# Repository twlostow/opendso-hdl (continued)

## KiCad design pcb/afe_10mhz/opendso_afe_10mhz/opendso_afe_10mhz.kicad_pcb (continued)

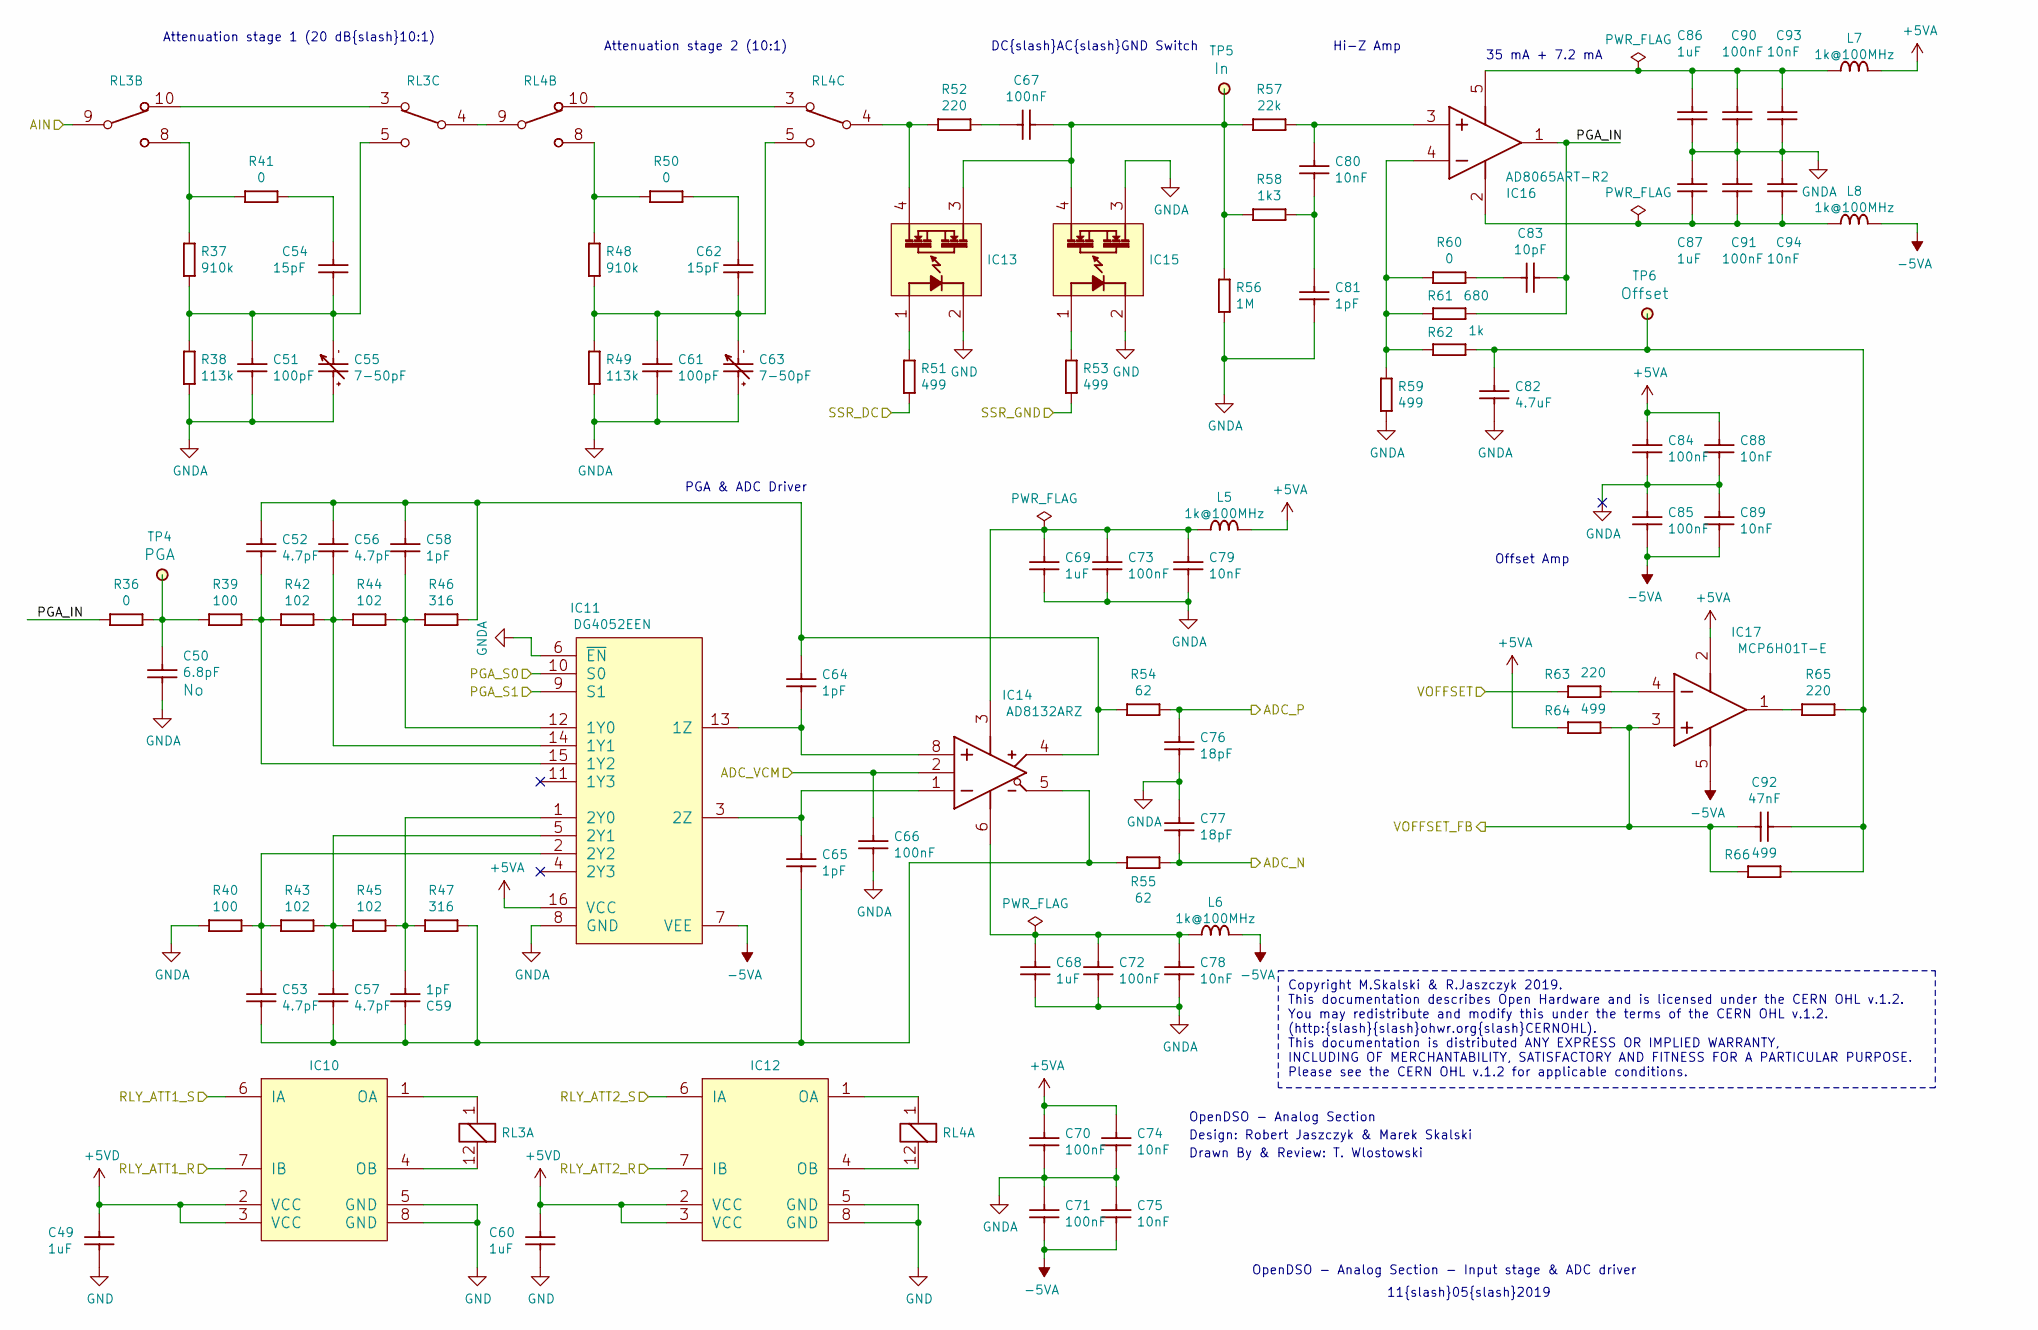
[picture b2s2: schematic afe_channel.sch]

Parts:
C49, C60, C68, C69, C86, C87: CC0603_1UF_16V_10%_X7R; CAPC1608X87N; Voltage 16V; Tolerance ±10%; Part Number CC0603_1UF_16V_10%_X7R
C50: CC0603_6.8PF_50V_0.5PF_NP0; CAPC1608X87N; Voltage 50V; Tolerance ±0.5pF; Part Number CC0603_6.8PF_50V_0.5PF_NP0
C51, C61: CC0603_100PF_50V_1%_NP0; CAPC1608X90N; Voltage 50V; Tolerance ±1%; Part Number CC0603_100PF_50V_1%_NP0
C52, C53, C56, C57: CC0603_4.7PF_50V_0.25PF_NP0; CAPC1608X87N; Voltage 50V; Tolerance ±0.25pF; Part Number CC0603_4.7PF_50V_0.25PF_NP0
C54, C62: CC0603_15PF_50V_5%_NP0; CAPC1608X87N; Voltage 50V; Tolerance ±5%; Part Number CC0603_15PF_50V_5%_NP0
C55, C63: CADJ_7-50PF_50V_MURATA_TZB4R500AB10R00; CAPV_MURATA_TZB4_TYPE A; Voltage 50V; Tolerance +100 -0%; Part Number CADJ_7-50PF_50V_MURATA_TZB4R500AB10R00
C58, C59, C64, C65, C81: CC0603_1PF_50V_0.25PF_NP0; CAPC1608X87N; Voltage 50V; Tolerance ±0.25pF; Part Number CC0603_1PF_50V_0.25PF_NP0
C66, C70, C71, C72, C73, C84, C85, C90, C91: CC0603_100NF_50V_10%_X7R; CAPC1608X87N; Voltage 50V; Tolerance ±10%; Part Number CC0603_100NF_50V_10%_X7R
C67: CC1206_100NF_100V_10%_X7R; CAPC3216X140N; Voltage 100V; Tolerance ±10%; Part Number CC1206_100NF_100V_10%_X7R
C74, C75, C78, C79, C80, C88, C89, C93, C94: CC0603_10NF_50V_5%_C0G; CAPC1608X87N; Voltage 50V; Tolerance ±5%; Part Number CC0603_10NF_50V_5%_C0G
C76, C77: CC0603_18PF_50V_5%_NP0; CAPC1608X87N; Voltage 50V; Tolerance ±5%; Part Number CC0603_18PF_50V_5%_NP0
C82: CC0805_4.7UF_16V_10%_X7R; CAPC2012X135N; Voltage 16V; Tolerance ±10%; Part Number CC0805_4.7UF_16V_10%_X7R
C83: CC0603_10PF_50V_5%_NP0; CAPC1608X87N; Voltage 50V; Tolerance ±5%; Part Number CC0603_10PF_50V_5%_NP0
C92: CC0603_47NF_25V_10%_X7R; CAPC1608X87N; Voltage 25V; Tolerance ±10%; Part Number CC0603_47NF_25V_10%_X7R
IC10, IC12: L9110; SOIC127P1030X265-20N; Part Number MC100LVEL14DWG
IC11: DG4052EEN; SOP65P640X110-16N; Part Number 74HCT4052PW
IC13, IC15: VO1400AEFTR; VISHAY_VO1400AEF; Part Number VO1400AEFTR
IC14: AD8132ARZ; SOIC127P600X175-8N; Part Number AD8132ARZ
IC16: AD8065ART-R2; SOT95P280X145-5N; Part Number AD8065ART-R2
IC17: MCP6H01T-E; SOT95P280X145-5N; Part Number MCP6H01T-E
L5, L6, L7, L8: IND0603_MURATA_BLM18AG102SN1; INDC1608X95N; Tolerance ±25%; Part Number IND0603_MURATA_BLM18AG102SN1
R36, R41, R50, R60: R0603_0R_JUMPER; RESC1608X55N; Voltage ~~; Tolerance ~~; Part Number R0603_0R_JUMPER
R37, R48: R0603_910K_1%_0.1W_100PPM; RESC1608X55N; Voltage ~~; Tolerance ±1%; Part Number R0603_910K_1%_0.1W_100PPM
R38, R49: R0603_113K_0.1%_0.063W_10PPM; RESC1608X55N; Voltage ~~; Tolerance ±0.1%; Part Number R0603_113K_0.1%_0.063W_10PPM
R39, R40: R0603_100R_1%_0.1W_100PPM; RESC1608X55N; Tolerance ±1%; Part Number R0603_100R_1%_0.1W_100PPM
R42, R43, R44, R45: R0603_102R_0.1%_0.063W_10PPM; RESC1608X55N; Tolerance ±0.1%; Part Number R0603_102R_0.1%_0.063W_10PPM
R46, R47: R0603_316R_0.1%_0.063W_10PPM; RESC1608X55N; Tolerance ±0.1%; Part Number R0603_316R_0.1%_0.063W_10PPM
R51, R53, R59, R64, R66: R0603_499R_0.1%_0.063W_10PPM; RESC1608X55N; Voltage ~~; Tolerance ±0.1%; Part Number R0603_499R_0.1%_0.063W_10PPM
R52, R63, R65: R0603_220R_1%_0.1W_100PPM; RESC1608X55N; Voltage ~~; Tolerance ±1%; Part Number R0603_220R_1%_0.1W_100PPM
R54, R55: R0603_62R_1%_0.1W_100PPM; RESC1608X55N; Tolerance ±1%; Part Number R0603_62R_1%_0.1W_100PPM
R56: R0603_1M_1%_0.1W_100PPM; RESC1608X55N; Voltage ~~; Tolerance ±1%; Part Number R0603_1M_1%_0.1W_100PPM
R57: R0603_22K_1%_0.1W_100PPM; RESC1608X55N; Voltage ~~; Tolerance ±1%; Part Number R0603_22K_1%_0.1W_100PPM
R58: R0603_1K3_1%_0.1W_100PPM; RESC1608X55N; Voltage ~~; Tolerance ±1%; Part Number R0603_1K3_1%_0.1W_100PPM
R61: R0603_680R_0.1%_0.1W_25PPM; RESC1608X64N; Voltage ~~; Tolerance ±0.1%; Part Number R0603_680R_0.1%_0.1W_25PPM
R62: R0603_1K_1%_0.1W_100PPM; RESC1608X55N; Voltage ~~; Tolerance ±1%; Part Number R0603_1K_1%_0.1W_100PPM
RL3, RL4: REL_OMRON_G6SU-2F-5VDC; Relay_DPDT_Omron_G6SU-2F; Part Description DPDT Signal Relay, Ultracompact and Ult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
TP4: PGA; TPS127; Part Number SMD_PAD_1.27X1.27MM
TP5: In; TPS127; Part Number SMD_PAD_1.27X1.27MM
TP6: Offset; TPS127; Part Number SMD_PAD_1.27X1.27MM

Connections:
+5VA: C70.2, C74.2, C84.2, C88.2, IC11.16 (VCC), IC17.2 (V-), L5.2, L7.2, R64.2; also elsewhere on the board
+5VD: C49.2, C60.2, IC10.2 (VCC), IC10.3 (VCC), IC12.2 (VCC), IC12.3 (VCC); also elsewhere on the board
-5VA: C71.1, C75.1, C85.1, C89.1, IC11.7 (VEE), IC17.5 (V+), L6.2, L8.2; also elsewhere on the board
/ADC_N: C77.1, R55.2; also elsewhere on the board
/ADC_P: C76.2, R54.2; also elsewhere on the board
/AFE Channel 1/PGA_IN: C83.2, IC16.1 (OUT), R36.1, R61.2
/AIN_1: RL3.9 (C); also elsewhere on the board
/CH1_PGA_S0: IC11.10 (S0); also elsewhere on the board
/CH1_PGA_S1: IC11.9 (S1); also elsewhere on the board
/CH1_RLY_ATT1_R: IC10.7 (IB); also elsewhere on the board
/CH1_RLY_ATT1_S: IC10.6 (IA); also elsewhere on the board
/CH1_RLY_ATT2_R: IC12.7 (IB); also elsewhere on the board
/CH1_RLY_ATT2_S: IC12.6 (IA); also elsewhere on the board
/CH1_SSR_DC: R51.1; also elsewhere on the board
/CH1_SSR_GND: R53.1; also elsewhere on the board
/CH1_VCM: C66.2, IC14.2 (VOCM); also elsewhere on the board
/CH1_VOFFSET: R63.1; also elsewhere on the board
/CH1_VOFFSET_FB: C92.1, IC17.3 (IN+), R64.1, R66.2; also elsewhere on the board
unnamed: C50.1, R36.2, R39.1, TP4.1
unnamed: C51.2, C54.1, C55.2, R37.1, R38.2, RL3.5 (NO)
unnamed: C52.1, IC11.15 (1Y2), R39.2, R42.1
unnamed: C52.2, C56.2, C58.2, C64.2, IC14.4 (VOUT+), R46.2, R54.1
unnamed: C53.1, C57.1, C59.2, C65.1, IC14.5 (VOUT-), R47.2, R55.1
unnamed: C53.2, IC11.2 (2Y2), R40.2, R43.1
unnamed: C54.2, R41.2
unnamed: C56.1, IC11.14 (1Y1), R42.2, R44.1
unnamed: C57.2, IC11.5 (2Y1), R43.2, R45.1
unnamed: C58.1, IC11.12 (1Y0), R44.2, R46.1
unnamed: C59.1, IC11.1 (2Y0), R45.2, R47.1
unnamed: C61.2, C62.1, C63.2, R48.1, R49.2, RL4.5 (NO)
unnamed: C62.2, R50.2
unnamed: C64.1, IC11.13 (1Z), IC14.8 (IN+)
unnamed: C65.2, IC11.3 (2Z), IC14.1 (IN-)
unnamed: C67.1, R52.2
unnamed: C67.2, IC13.3 (C), IC15.4 (E), R56.2, R57.1, R58.1, TP5.1
unnamed: C68.2, C72.2, C78.2, IC14.6 (V-), L6.1
unnamed: C69.2, C73.2, C79.2, IC14.3 (V+), L5.1
unnamed: C80.1, C81.2, R58.2
unnamed: C80.2, IC16.3 (IN+), R57.2
unnamed: C82.2, C92.2, R62.2, R65.2, R66.1, TP6.1
unnamed: C83.1, R60.2
unnamed: C86.2, C90.2, C93.2, IC16.5 (V+), L7.1
unnamed: C87.1, C91.1, C94.1, IC16.2 (V-), L8.1
unnamed: IC10.1 (OA), RL3.1
unnamed: IC10.4 (OB), RL3.12
unnamed: IC12.1 (OA), RL4.1
unnamed: IC12.4 (OB), RL4.12
unnamed: IC13.1 (A), R51.2
unnamed: IC13.4 (E), R52.1, RL4.4 (C)
unnamed: IC15.1 (A), R53.2
unnamed: IC16.4 (IN-), R59.2, R60.1, R61.1, R62.1
unnamed: IC17.1 (OUT), R65.1
unnamed: IC17.4 (IN-), R63.2
unnamed: R37.2, R41.1, RL3.8 (NO)
unnamed: R48.2, R50.1, RL4.8 (NO)
unnamed: RL3.4 (C), RL4.9 (C)
unnamed: RL3.3 (NC), RL3.10 (NC)
unnamed: RL4.3 (NC), RL4.10 (NC)

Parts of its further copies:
C3, C14, C22, C23, C40, C41: CC0603_1UF_16V_10%_X7R; CAPC1608X87N; Voltage 16V; Tolerance ±10%; Part Number CC0603_1UF_16V_10%_X7R
C4: CC0603_6.8PF_50V_0.5PF_NP0; CAPC1608X87N; Voltage 50V; Tolerance ±0.5pF; Part Number CC0603_6.8PF_50V_0.5PF_NP0
C5, C15: CC0603_100PF_50V_1%_NP0; CAPC1608X90N; Voltage 50V; Tolerance ±1%; Part Number CC0603_100PF_50V_1%_NP0
C6, C7, C10, C11: CC0603_4.7PF_50V_0.25PF_NP0; CAPC1608X87N; Voltage 50V; Tolerance ±0.25pF; Part Number CC0603_4.7PF_50V_0.25PF_NP0
C8, C16: CC0603_15PF_50V_5%_NP0; CAPC1608X87N; Voltage 50V; Tolerance ±5%; Part Number CC0603_15PF_50V_5%_NP0
C9, C17: CADJ_7-50PF_50V_MURATA_TZB4R500AB10R00; CAPV_MURATA_TZB4_TYPE A; Voltage 50V; Tolerance +100 -0%; Part Number CADJ_7-50PF_50V_MURATA_TZB4R500AB10R00
C12, C13, C18, C19, C35: CC0603_1PF_50V_0.25PF_NP0; CAPC1608X87N; Voltage 50V; Tolerance ±0.25pF; Part Number CC0603_1PF_50V_0.25PF_NP0
C20, C24, C25, C26, C27, C38, C39, C44, C45: CC0603_100NF_50V_10%_X7R; CAPC1608X87N; Voltage 50V; Tolerance ±10%; Part Number CC0603_100NF_50V_10%_X7R
C21: CC1206_100NF_100V_10%_X7R; CAPC3216X140N; Voltage 100V; Tolerance ±10%; Part Number CC1206_100NF_100V_10%_X7R
C28, C29, C32, C33, C34, C42, C43, C47, C48: CC0603_10NF_50V_5%_C0G; CAPC1608X87N; Voltage 50V; Tolerance ±5%; Part Number CC0603_10NF_50V_5%_C0G
C30, C31: CC0603_18PF_50V_5%_NP0; CAPC1608X87N; Voltage 50V; Tolerance ±5%; Part Number CC0603_18PF_50V_5%_NP0
C36: CC0805_4.7UF_16V_10%_X7R; CAPC2012X135N; Voltage 16V; Tolerance ±10%; Part Number CC0805_4.7UF_16V_10%_X7R
C37: CC0603_10PF_50V_5%_NP0; CAPC1608X87N; Voltage 50V; Tolerance ±5%; Part Number CC0603_10PF_50V_5%_NP0
C46: CC0603_47NF_25V_10%_X7R; CAPC1608X87N; Voltage 25V; Tolerance ±10%; Part Number CC0603_47NF_25V_10%_X7R
IC2, IC4: L9110; SOIC127P1030X265-20N; Part Number MC100LVEL14DWG
IC3: DG4052EEN; SOP65P640X110-16N; Part Number 74HCT4052PW
IC5, IC7: VO1400AEFTR; VISHAY_VO1400AEF; Part Number VO1400AEFTR
IC6: AD8132ARZ; SOIC127P600X175-8N; Part Number AD8132ARZ
IC8: AD8065ART-R2; SOT95P280X145-5N; Part Number AD8065ART-R2
IC9: MCP6H01T-E; SOT95P280X145-5N; Part Number MCP6H01T-E
L1, L2, L3, L4: IND0603_MURATA_BLM18AG102SN1; INDC1608X95N; Tolerance ±25%; Part Number IND0603_MURATA_BLM18AG102SN1
R5, R10, R19, R29: R0603_0R_JUMPER; RESC1608X55N; Voltage ~~; Tolerance ~~; Part Number R0603_0R_JUMPER
R6, R17: R0603_910K_1%_0.1W_100PPM; RESC1608X55N; Voltage ~~; Tolerance ±1%; Part Number R0603_910K_1%_0.1W_100PPM
R7, R18: R0603_113K_0.1%_0.063W_10PPM; RESC1608X55N; Voltage ~~; Tolerance ±0.1%; Part Number R0603_113K_0.1%_0.063W_10PPM
R8, R9: R0603_100R_1%_0.1W_100PPM; RESC1608X55N; Tolerance ±1%; Part Number R0603_100R_1%_0.1W_100PPM
R11, R12, R13, R14: R0603_102R_0.1%_0.063W_10PPM; RESC1608X55N; Tolerance ±0.1%; Part Number R0603_102R_0.1%_0.063W_10PPM
R15, R16: R0603_316R_0.1%_0.063W_10PPM; RESC1608X55N; Tolerance ±0.1%; Part Number R0603_316R_0.1%_0.063W_10PPM
R20, R22, R28, R33, R35: R0603_499R_0.1%_0.063W_10PPM; RESC1608X55N; Voltage ~~; Tolerance ±0.1%; Part Number R0603_499R_0.1%_0.063W_10PPM
R21, R32, R34: R0603_220R_1%_0.1W_100PPM; RESC1608X55N; Voltage ~~; Tolerance ±1%; Part Number R0603_220R_1%_0.1W_100PPM
R23, R24: R0603_62R_1%_0.1W_100PPM; RESC1608X55N; Tolerance ±1%; Part Number R0603_62R_1%_0.1W_100PPM
R25: R0603_1M_1%_0.1W_100PPM; RESC1608X55N; Voltage ~~; Tolerance ±1%; Part Number R0603_1M_1%_0.1W_100PPM
R26: R0603_22K_1%_0.1W_100PPM; RESC1608X55N; Voltage ~~; Tolerance ±1%; Part Number R0603_22K_1%_0.1W_100PPM
R27: R0603_1K3_1%_0.1W_100PPM; RESC1608X55N; Voltage ~~; Tolerance ±1%; Part Number R0603_1K3_1%_0.1W_100PPM
R30: R0603_680R_0.1%_0.1W_25PPM; RESC1608X64N; Voltage ~~; Tolerance ±0.1%; Part Number R0603_680R_0.1%_0.1W_25PPM
R31: R0603_1K_1%_0.1W_100PPM; RESC1608X55N; Voltage ~~; Tolerance ±1%; Part Number R0603_1K_1%_0.1W_100PPM
RL1, RL2: REL_OMRON_G6SU-2F-5VDC; Relay_DPDT_Omron_G6SU-2F; Part Description DPDT Signal Relay, Ultracompact and Ult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
TP1: PGA; TPS127; Part Number SMD_PAD_1.27X1.27MM
TP2: In; TPS127; Part Number SMD_PAD_1.27X1.27MM
TP3: Offset; TPS127; Part Number SMD_PAD_1.27X1.27MM

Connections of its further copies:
+5VA: C24.2, C28.2, C38.2, C42.2, IC3.16 (VCC), IC9.2 (V-), L1.2, L3.2, R33.2; also elsewhere on the board
+5VD: C3.2, C14.2, IC2.2 (VCC), IC2.3 (VCC), IC4.2 (VCC), IC4.3 (VCC); also elsewhere on the board
-5VA: C25.1, C29.1, C39.1, C43.1, IC3.7 (VEE), IC9.5 (V+), L2.2, L4.2; also elsewhere on the board
/ADC_N_1: C31.1, R24.2; also elsewhere on the board
/ADC_P_1: C30.2, R23.2; also elsewhere on the board
/AFE Channel 2/PGA_IN: C37.2, IC8.1 (OUT), R5.1, R30.2
/AIN: RL1.9 (C); also elsewhere on the board
/CH2_PGA_S0: IC3.10 (S0); also elsewhere on the board
/CH2_PGA_S1: IC3.9 (S1); also elsewhere on the board
/CH2_RLY_ATT1_R: IC2.7 (IB); also elsewhere on the board
/CH2_RLY_ATT1_S: IC2.6 (IA); also elsewhere on the board
/CH2_RLY_ATT2_R: IC4.6 (IA); also elsewhere on the board
/CH2_RLY_ATT2_S: IC4.7 (IB); also elsewhere on the board
/CH2_SSR_DC: R20.1; also elsewhere on the board
/CH2_SSR_GND: R22.1; also elsewhere on the board
/CH2_VCM: C20.2, IC6.2 (VOCM); also elsewhere on the board
/CH2_VOFFSET: R32.1; also elsewhere on the board
/CH2_VOFFSET_FB: C46.1, IC9.3 (IN+), R33.1, R35.2; also elsewhere on the board
unnamed: C4.1, R5.2, R8.1, TP1.1
unnamed: C5.2, C8.1, C9.2, R6.1, R7.2, RL1.5 (NO)
unnamed: C6.1, IC3.15 (1Y2), R8.2, R11.1
unnamed: C7.2, IC3.2 (2Y2), R9.2, R12.1
unnamed: C8.2, R10.2
unnamed: C10.1, IC3.14 (1Y1), R11.2, R13.1
unnamed: C6.2, C10.2, C12.2, C18.2, IC6.4 (VOUT+), R15.2, R23.1
unnamed: C7.1, C11.1, C13.2, C19.1, IC6.5 (VOUT-), R16.2, R24.1
unnamed: C11.2, IC3.5 (2Y1), R12.2, R14.1
unnamed: C12.1, IC3.12 (1Y0), R13.2, R15.1
unnamed: C13.1, IC3.1 (2Y0), R14.2, R16.1
unnamed: C15.2, C16.1, C17.2, R17.1, R18.2, RL2.5 (NO)
unnamed: C16.2, R19.2
unnamed: C18.1, IC3.13 (1Z), IC6.8 (IN+)
unnamed: C19.2, IC3.3 (2Z), IC6.1 (IN-)
unnamed: C21.1, R21.2
unnamed: C21.2, IC5.3 (C), IC7.4 (E), R25.2, R26.1, R27.1, TP2.1
unnamed: C22.2, C26.2, C32.2, IC6.6 (V-), L2.1
unnamed: C23.2, C27.2, C33.2, IC6.3 (V+), L1.1
unnamed: C34.1, C35.2, R27.2
unnamed: C34.2, IC8.3 (IN+), R26.2
unnamed: C36.2, C46.2, R31.2, R34.2, R35.1, TP3.1
unnamed: C37.1, R29.2
unnamed: C40.2, C44.2, C47.2, IC8.5 (V+), L3.1
unnamed: C41.1, C45.1, C48.1, IC8.2 (V-), L4.1
unnamed: IC2.1 (OA), RL1.1
unnamed: IC2.4 (OB), RL1.12
unnamed: IC4.1 (OA), RL2.1
unnamed: IC4.4 (OB), RL2.12
unnamed: IC5.1 (A), R20.2
unnamed: IC5.4 (E), R21.1, RL2.4 (C)
unnamed: IC7.1 (A), R22.2
unnamed: IC8.4 (IN-), R28.2, R29.1, R30.1, R31.1
unnamed: IC9.1 (OUT), R34.1
unnamed: IC9.4 (IN-), R32.2
unnamed: R6.2, R10.1, RL1.8 (NO)
unnamed: R17.2, R19.1, RL2.8 (NO)
unnamed: RL1.4 (C), RL2.9 (C)
unnamed: RL1.3 (NC), RL1.10 (NC)
unnamed: RL2.3 (NC), RL2.10 (NC)

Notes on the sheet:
Attenuation stage 2 (10:1)
Attenuation stage 1 (20 dB{slash}10:1)
DC{slash}AC{slash}GND Switch
Hi-Z Amp
Offset Amp
PGA & ADC Driver
35 mA + 7.2 mA
Copyright M.Skalski & R.Jaszczyk 2019. This documentation describes Open Hardware and is licensed under the CERN OHL v.1.2. You may redistribute and modify this under the terms of the CERN OHL v.1.2. (http:{slash}{slash}ohwr.org{slash}CERNOHL). This documentation is distributed ANY EXPRESS OR IMPLI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
11{slash}05{slash}2019
OpenDSO - Analog Section - Input stage & ADC driver
Design: Robert Jaszczyk & Marek Skalski
OpenDSO - Analog Section
Drawn By & Review: T. Wlostowski

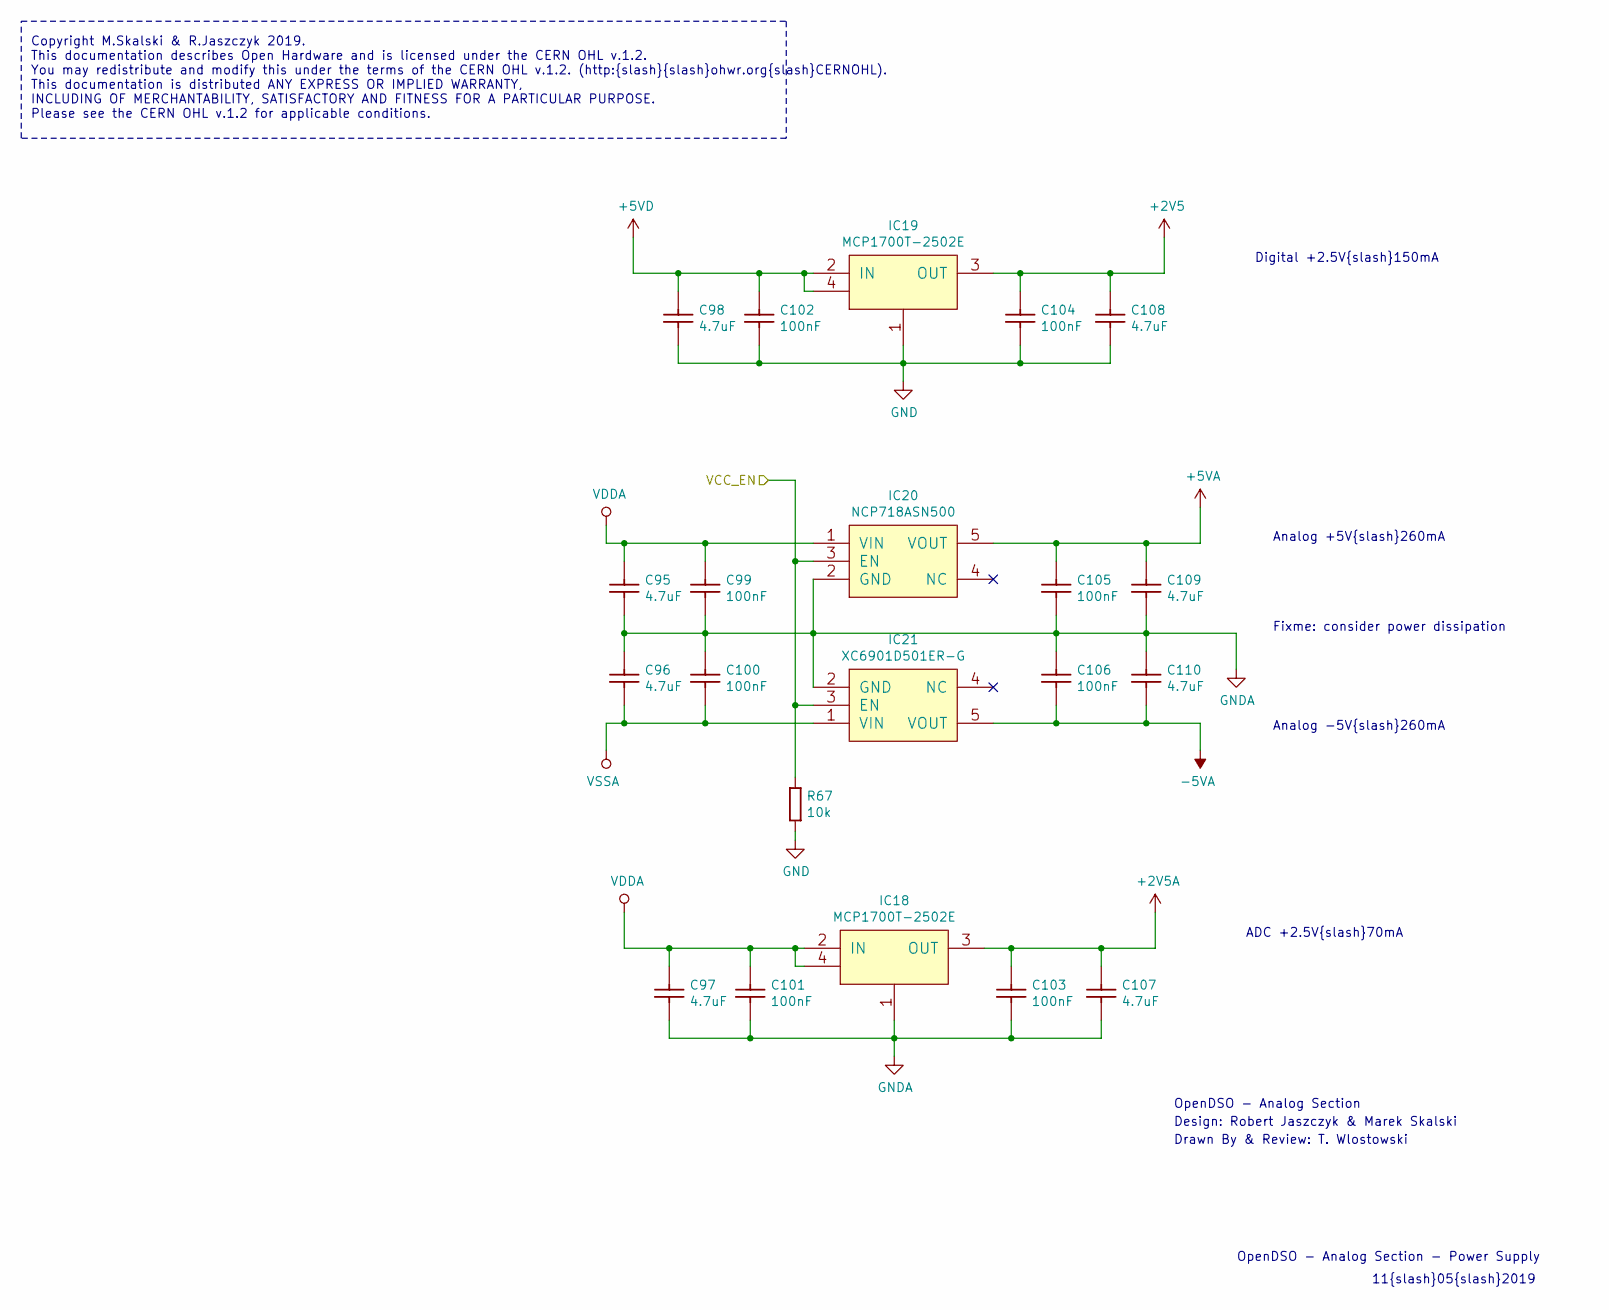
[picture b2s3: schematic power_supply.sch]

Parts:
C95, C96, C97, C98, C107, C108, C109, C110: CC0805_4.7UF_16V_10%_X7R; CAPC2012X135N; Voltage 16V; Tolerance ±10%; Part Number CC0805_4.7UF_16V_10%_X7R
C99, C100, C101, C102, C103, C104, C105, C106: CC0603_100NF_50V_10%_X5R; CAPC1608X87N; Voltage 50V; Tolerance ±10%; Part Number CC0603_100NF_50V_10%_X5R
IC18, IC19: MCP1700T-2502E; SOT230P700X180-4N; Part Number MCP1700T-2502E
IC20: NCP718ASN500; SOT95P275X110-5N; Part Number NCP718ASN500
IC21: XC6901D501ER-G; SOT95P275X110-5N; Part Number XC6901D501ER-G
R67: R0603_10K_1%_0.1W_100PPM; RESC1608X55N; Tolerance ±1%; Part Number R0603_10K_1%_0.1W_100PPM

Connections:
+2V5: C104.2, C108.2, IC19.3 (OUT); also elsewhere on the board
+2V5A: C103.2, C107.2, IC18.3 (OUT); also elsewhere on the board
+5VA: C105.2, C109.2, IC20.5 (VOUT); also elsewhere on the board
+5VD: C98.2, C102.2, IC19.2 (IN), IC19.4 (OUT); also elsewhere on the board
-5VA: C106.1, C110.1, IC21.5 (VOUT); also elsewhere on the board
/VCC_EN: IC20.3 (EN), IC21.3 (EN), R67.2; also elsewhere on the board
VDDA: C95.2, C97.2, C99.2, C101.2, IC18.2 (IN), IC18.4 (OUT), IC20.1 (VIN); also elsewhere on the board
VSSA: C96.1, C100.1, IC21.1 (VIN); also elsewhere on the board

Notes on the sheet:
11{slash}05{slash}2019
OpenDSO - Analog Section - Power Supply
OpenDSO - Analog Section
Drawn By & Review: T. Wlostowski
Design: Robert Jaszczyk & Marek Skalski
ADC +2.5V{slash}70mA
Digital +2.5V{slash}150mA
Analog -5V{slash}260mA
Analog +5V{slash}260mA
Copyright M.Skalski & R.Jaszczyk 2019. This documentation describes Open Hardware and is licensed under the CERN OHL v.1.2. You may redistribute and modify this under the terms of the CERN OHL v.1.2. (http:{slash}{slash}ohwr.org{slash}CERNOHL). This documentation is distributed ANY EXPRESS OR IMPLI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
Fixme: consider power dissipation

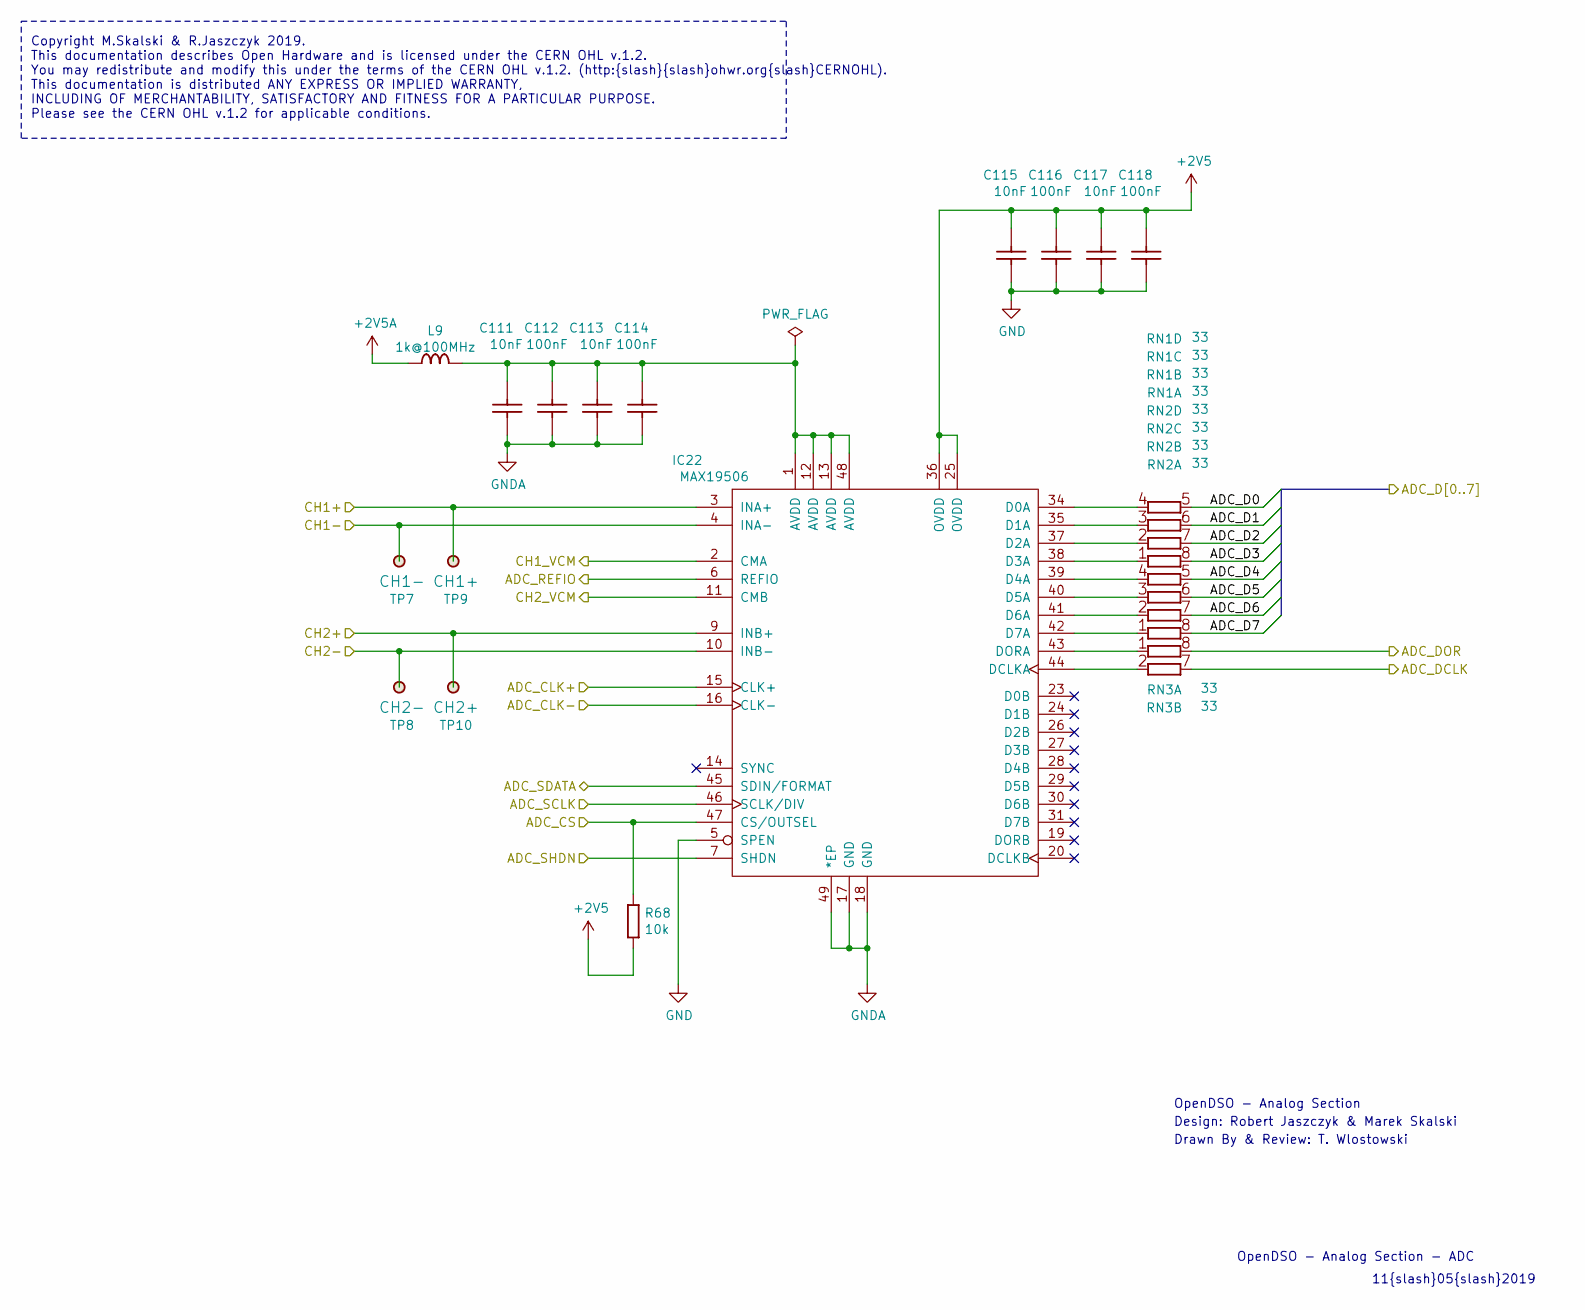
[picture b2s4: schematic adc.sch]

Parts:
C111, C113, C115, C117: CC0603_10NF_50V_5%_C0G; CAPC1608X87N; Voltage 50V; Tolerance ±5%; Part Number CC0603_10NF_50V_5%_C0G
C112, C114, C116, C118: CC0603_100NF_50V_10%_X7R; CAPC1608X87N; Voltage 50V; Tolerance ±10%; Part Number CC0603_100NF_50V_10%_X7R
IC22: MAX19506; TQFP-48-1EP_7x7mm_Pitch0.5mm
L9: IND0603_MURATA_BLM18AG102SN1; INDC1608X95N; Tolerance ±25%; Part Number IND0603_MURATA_BLM18AG102SN1
R68: R0603_10K_1%_0.1W_100PPM; RESC1608X55N; Tolerance ±1%; Part Number R0603_10K_1%_0.1W_100PPM
RN1, RN2, RN3: RN_33R_YAGEO_TC164-FR-0733RL; RN_YAGEO_TC164; Tolerance ±1%; Part Number RN_33R_YAGEO_TC164-FR-0733RL
TP7: CH1-; TPS127; Part Number SMD_PAD_1.27X1.27MM
TP8: CH2-; TPS127; Part Number SMD_PAD_1.27X1.27MM
TP9: CH1+; TPS127; Part Number SMD_PAD_1.27X1.27MM
TP10: CH2+; TPS127; Part Number SMD_PAD_1.27X1.27MM

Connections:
+2V5: C115.2, C116.2, C117.2, C118.2, IC22.25 (OVDD), IC22.36 (OVDD), R68.1; also elsewhere on the board
+2V5A: L9.2; also elsewhere on the board
/ADC_CLK_N: IC22.16 (CLK-); also elsewhere on the board
/ADC_CLK_P: IC22.15 (CLK+); also elsewhere on the board
/ADC_CS_N: IC22.47 (CS/OUTSEL), R68.2; also elsewhere on the board
/ADC_D0: RN1.5; also elsewhere on the board
/ADC_D1: RN1.6; also elsewhere on the board
/ADC_D2: RN1.7; also elsewhere on the board
/ADC_D3: RN1.8; also elsewhere on the board
/ADC_D4: RN2.5; also elsewhere on the board
/ADC_D5: RN2.6; also elsewhere on the board
/ADC_D6: RN2.7; also elsewhere on the board
/ADC_D7: RN2.8; also elsewhere on the board
/ADC_DOR: RN3.8; also elsewhere on the board
/ADC_N: IC22.4 (INA-), TP7.1; also elsewhere on the board
/ADC_N_1: IC22.10 (INB-), TP8.1; also elsewhere on the board
/ADC_P: IC22.3 (INA+), TP9.1; also elsewhere on the board
/ADC_P_1: IC22.9 (INB+), TP10.1; also elsewhere on the board
/ADC_REFIO: IC22.6 (REFIO); also elsewhere on the board
/ADC_SCK: IC22.46 (SCLK/DIV); also elsewhere on the board
/ADC_SDATA: IC22.45 (SDIN/FORMAT); also elsewhere on the board
/ADC_SHDN: IC22.7 (SHDN); also elsewhere on the board
/CH1_VCM: IC22.2 (CMA); also elsewhere on the board
/CH2_VCM: IC22.11 (CMB); also elsewhere on the board
unnamed: C111.2, C112.2, C113.2, C114.2, IC22.1 (AVDD), IC22.12 (AVDD), IC22.13 (AVDD), IC22.48 (AVDD), L9.1
unnamed: IC22.34 (D0A), RN1.4
unnamed: IC22.35 (D1A), RN1.3
unnamed: IC22.37 (D2A), RN1.2
unnamed: IC22.38 (D3A), RN1.1
unnamed: IC22.39 (D4A), RN2.4
unnamed: IC22.40 (D5A), RN2.3
unnamed: IC22.41 (D6A), RN2.2
unnamed: IC22.42 (D7A), RN2.1
unnamed: IC22.43 (DORA), RN3.1
unnamed: IC22.44 (DCLKA), RN3.2

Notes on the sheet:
11{slash}05{slash}2019
OpenDSO - Analog Section - ADC
Design: Robert Jaszczyk & Marek Skalski
OpenDSO - Analog Section
Drawn By & Review: T. Wlostowski
Copyright M.Skalski & R.Jaszczyk 2019. This documentation describes Open Hardware and is licensed under the CERN OHL v.1.2. You may redistribute and modify this under the terms of the CERN OHL v.1.2. (http:{slash}{slash}ohwr.org{slash}CERNOHL). This documentation is distributed ANY EXPRESS OR IMPLI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

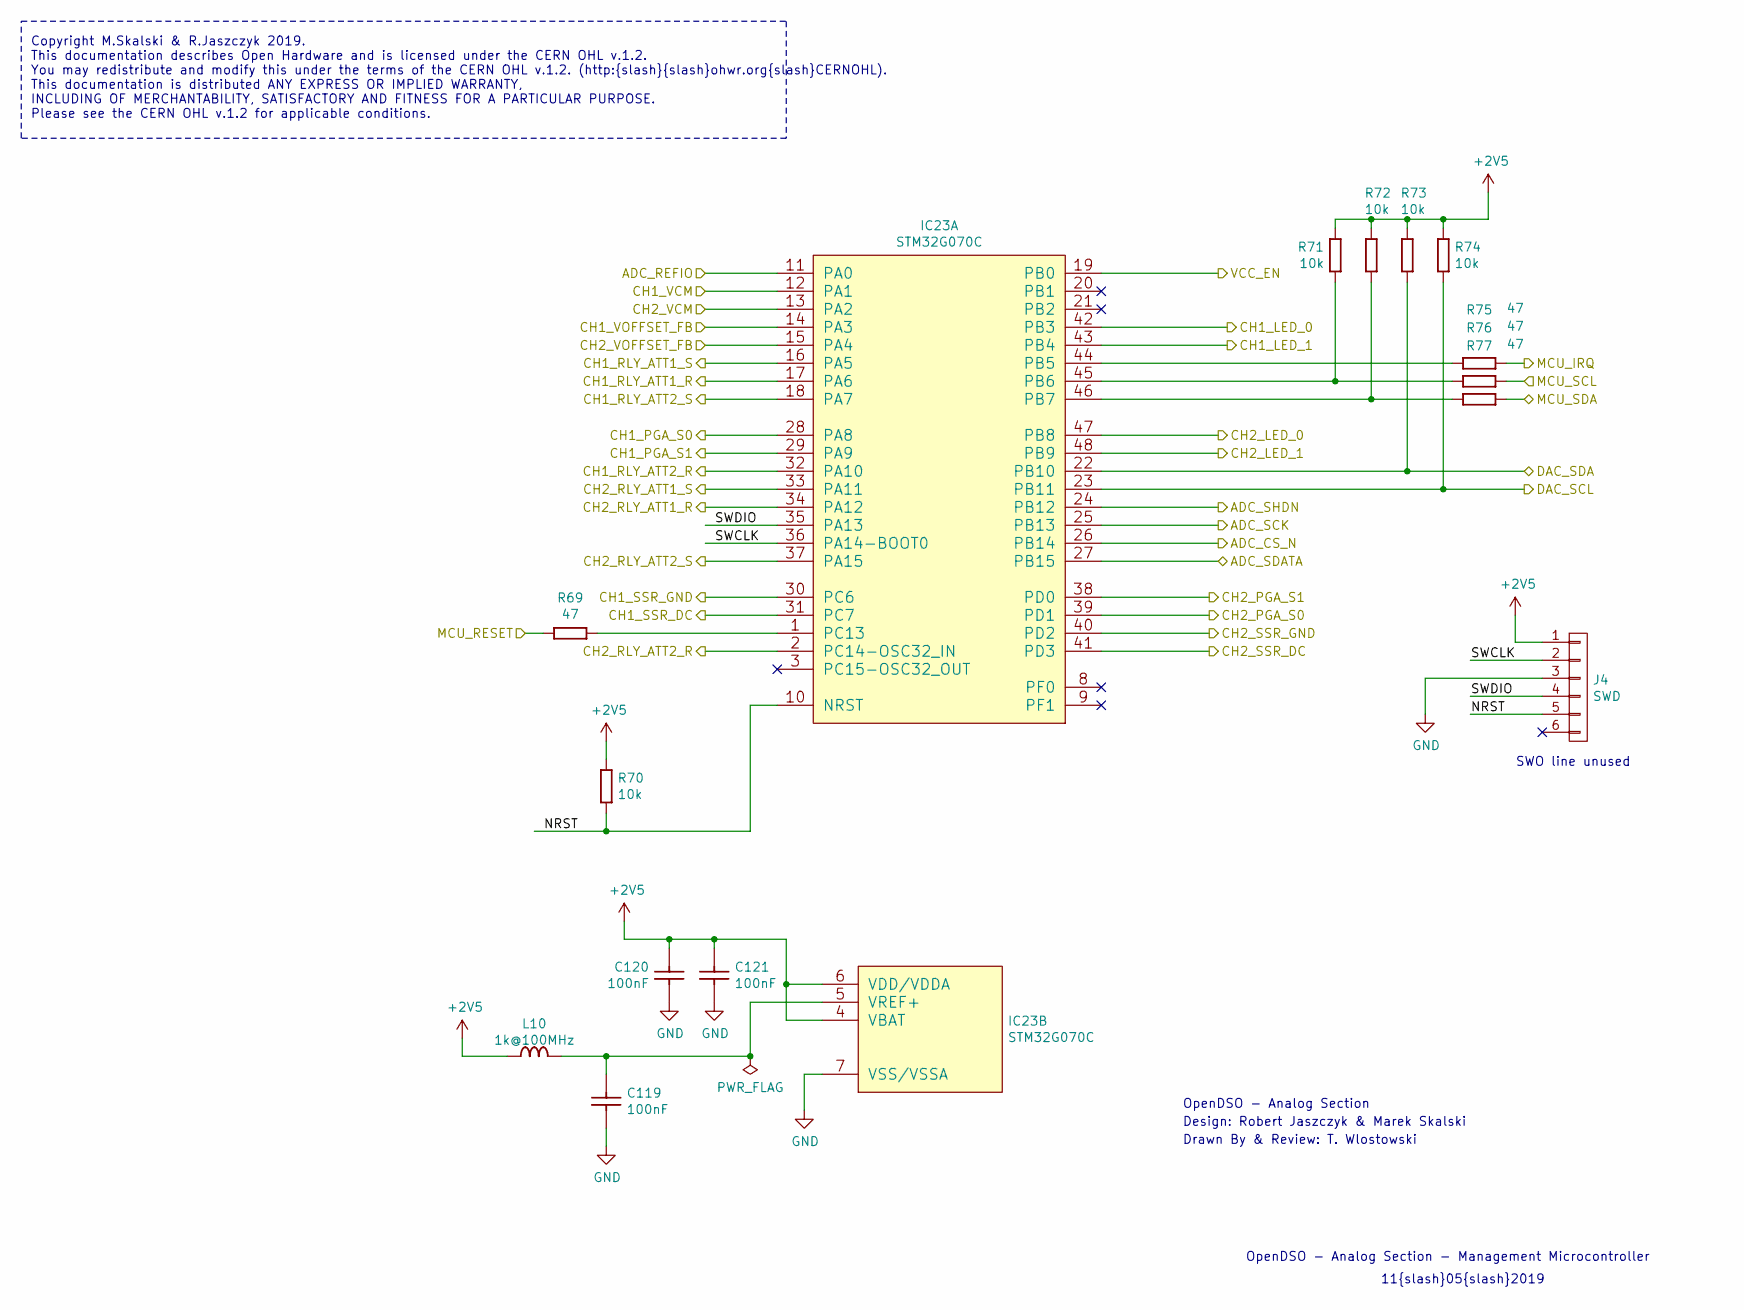
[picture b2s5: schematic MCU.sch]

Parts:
C119, C120, C121: CC0603_100NF_50V_10%_X7R; CAPC1608X87N; Voltage 50V; Tolerance ±10%; Part Number CC0603_100NF_50V_10%_X7R
IC23: STM32G070C; QFP50P900X900X160-48N; Part Number STM32F103CBT6
J4: SWD; PinHeader_1x06_P2.54mm_Vertical
L10: IND0603_MURATA_BLM18AG102SN1; INDC1608X95N; Tolerance ±25%; Part Number IND0603_MURATA_BLM18AG102SN1
R69, R75, R76, R77: R0603_47R_1%_0.1W_100PPM; RESC1608X55N; Tolerance ±1%; Part Number R0603_47R_1%_0.1W_100PPM
R70, R71, R72, R73, R74: R0603_10K_1%_0.1W_100PPM; RESC1608X55N; Tolerance ±1%; Part Number R0603_10K_1%_0.1W_100PPM

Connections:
+2V5: C120.2, C121.2, IC23.4 (VBAT), IC23.6 (VDD/VDDA), J4.1, L10.2, R70.2, R71.2, R72.2, R73.2, R74.2; also elsewhere on the board
/ADC_CS_N: IC23.26 (PB14); also elsewhere on the board
/ADC_REFIO: IC23.11 (PA0); also elsewhere on the board
/ADC_SCK: IC23.25 (PB13); also elsewhere on the board
/ADC_SDATA: IC23.27 (PB15); also elsewhere on the board
/ADC_SHDN: IC23.24 (PB12); also elsewhere on the board
/CH1_LED_0: IC23.42 (PB3); also elsewhere on the board
/CH1_LED_1: IC23.43 (PB4); also elsewhere on the board
/CH1_PGA_S0: IC23.28 (PA8); also elsewhere on the board
/CH1_PGA_S1: IC23.29 (PA9); also elsewhere on the board
/CH1_RLY_ATT1_R: IC23.17 (PA6); also elsewhere on the board
/CH1_RLY_ATT1_S: IC23.16 (PA5); also elsewhere on the board
/CH1_RLY_ATT2_R: IC23.32 (PA10); also elsewhere on the board
/CH1_RLY_ATT2_S: IC23.18 (PA7); also elsewhere on the board
/CH1_SSR_DC: IC23.31 (PC7); also elsewhere on the board
/CH1_SSR_GND: IC23.30 (PC6); also elsewhere on the board
/CH1_VCM: IC23.12 (PA1); also elsewhere on the board
/CH1_VOFFSET_FB: IC23.14 (PA3); also elsewhere on the board
/CH2_LED_0: IC23.47 (PB8); also elsewhere on the board
/CH2_LED_1: IC23.48 (PB9); also elsewhere on the board
/CH2_PGA_S0: IC23.39 (PD1); also elsewhere on the board
/CH2_PGA_S1: IC23.38 (PD0); also elsewhere on the board
/CH2_RLY_ATT1_R: IC23.34 (PA12); also elsewhere on the board
/CH2_RLY_ATT1_S: IC23.33 (PA11); also elsewhere on the board
/CH2_RLY_ATT2_R: IC23.2 (PC14-OSC32_IN); also elsewhere on the board
/CH2_RLY_ATT2_S: IC23.37 (PA15); also elsewhere on the board
/CH2_SSR_DC: IC23.41 (PD3); also elsewhere on the board
/CH2_SSR_GND: IC23.40 (PD2); also elsewhere on the board
/CH2_VCM: IC23.13 (PA2); also elsewhere on the board
/CH2_VOFFSET_FB: IC23.15 (PA4); also elsewhere on the board
/DAC_SCL: IC23.22 (PB10), R73.1; also elsewhere on the board
/DAC_SDA: IC23.23 (PB11), R74.1; also elsewhere on the board
/MCU/NRST: IC23.10 (NRST), J4.5, R70.1
/MCU/SWCLK: IC23.36 (PA14-BOOT0), J4.2
/MCU/SWDIO: IC23.35 (PA13), J4.4
/MCU_IRQ: R75.2; also elsewhere on the board
/MCU_RESET: R69.1; also elsewhere on the board
/MCU_SCL: R76.2; also elsewhere on the board
/MCU_SDA: R77.2; also elsewhere on the board
/VCC_EN: IC23.19 (PB0); also elsewhere on the board
unnamed: C119.2, IC23.5 (VREF+), L10.1
unnamed: IC23.1 (PC13), R69.2
unnamed: IC23.44 (PB5), R75.1
unnamed: IC23.45 (PB6), R71.1, R76.1
unnamed: IC23.46 (PB7), R72.1, R77.1

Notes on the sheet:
SWO line unused
Copyright M.Skalski & R.Jaszczyk 2019. This documentation describes Open Hardware and is licensed under the CERN OHL v.1.2. You may redistribute and modify this under the terms of the CERN OHL v.1.2. (http:{slash}{slash}ohwr.org{slash}CERNOHL). This documentation is distributed ANY EXPRESS OR IMPLI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
11{slash}05{slash}2019
OpenDSO - Analog Section - Management Microcontroller
Design: Robert Jaszczyk & Marek Skalski
OpenDSO - Analog Section
Drawn By & Review: T. Wlostowski

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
